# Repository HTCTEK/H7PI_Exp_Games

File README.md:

# H7PI_Exp_Games
expansion board for H7PI to use some sensors and oled

### Branch
1. master: with 1.3' oled display
2. H7PI_Exp_Games_tft: with 1.1' tft display

### Buy One
[ali taobao](https://item.taobao.com/item.htm?ft=t&id=609836748787)

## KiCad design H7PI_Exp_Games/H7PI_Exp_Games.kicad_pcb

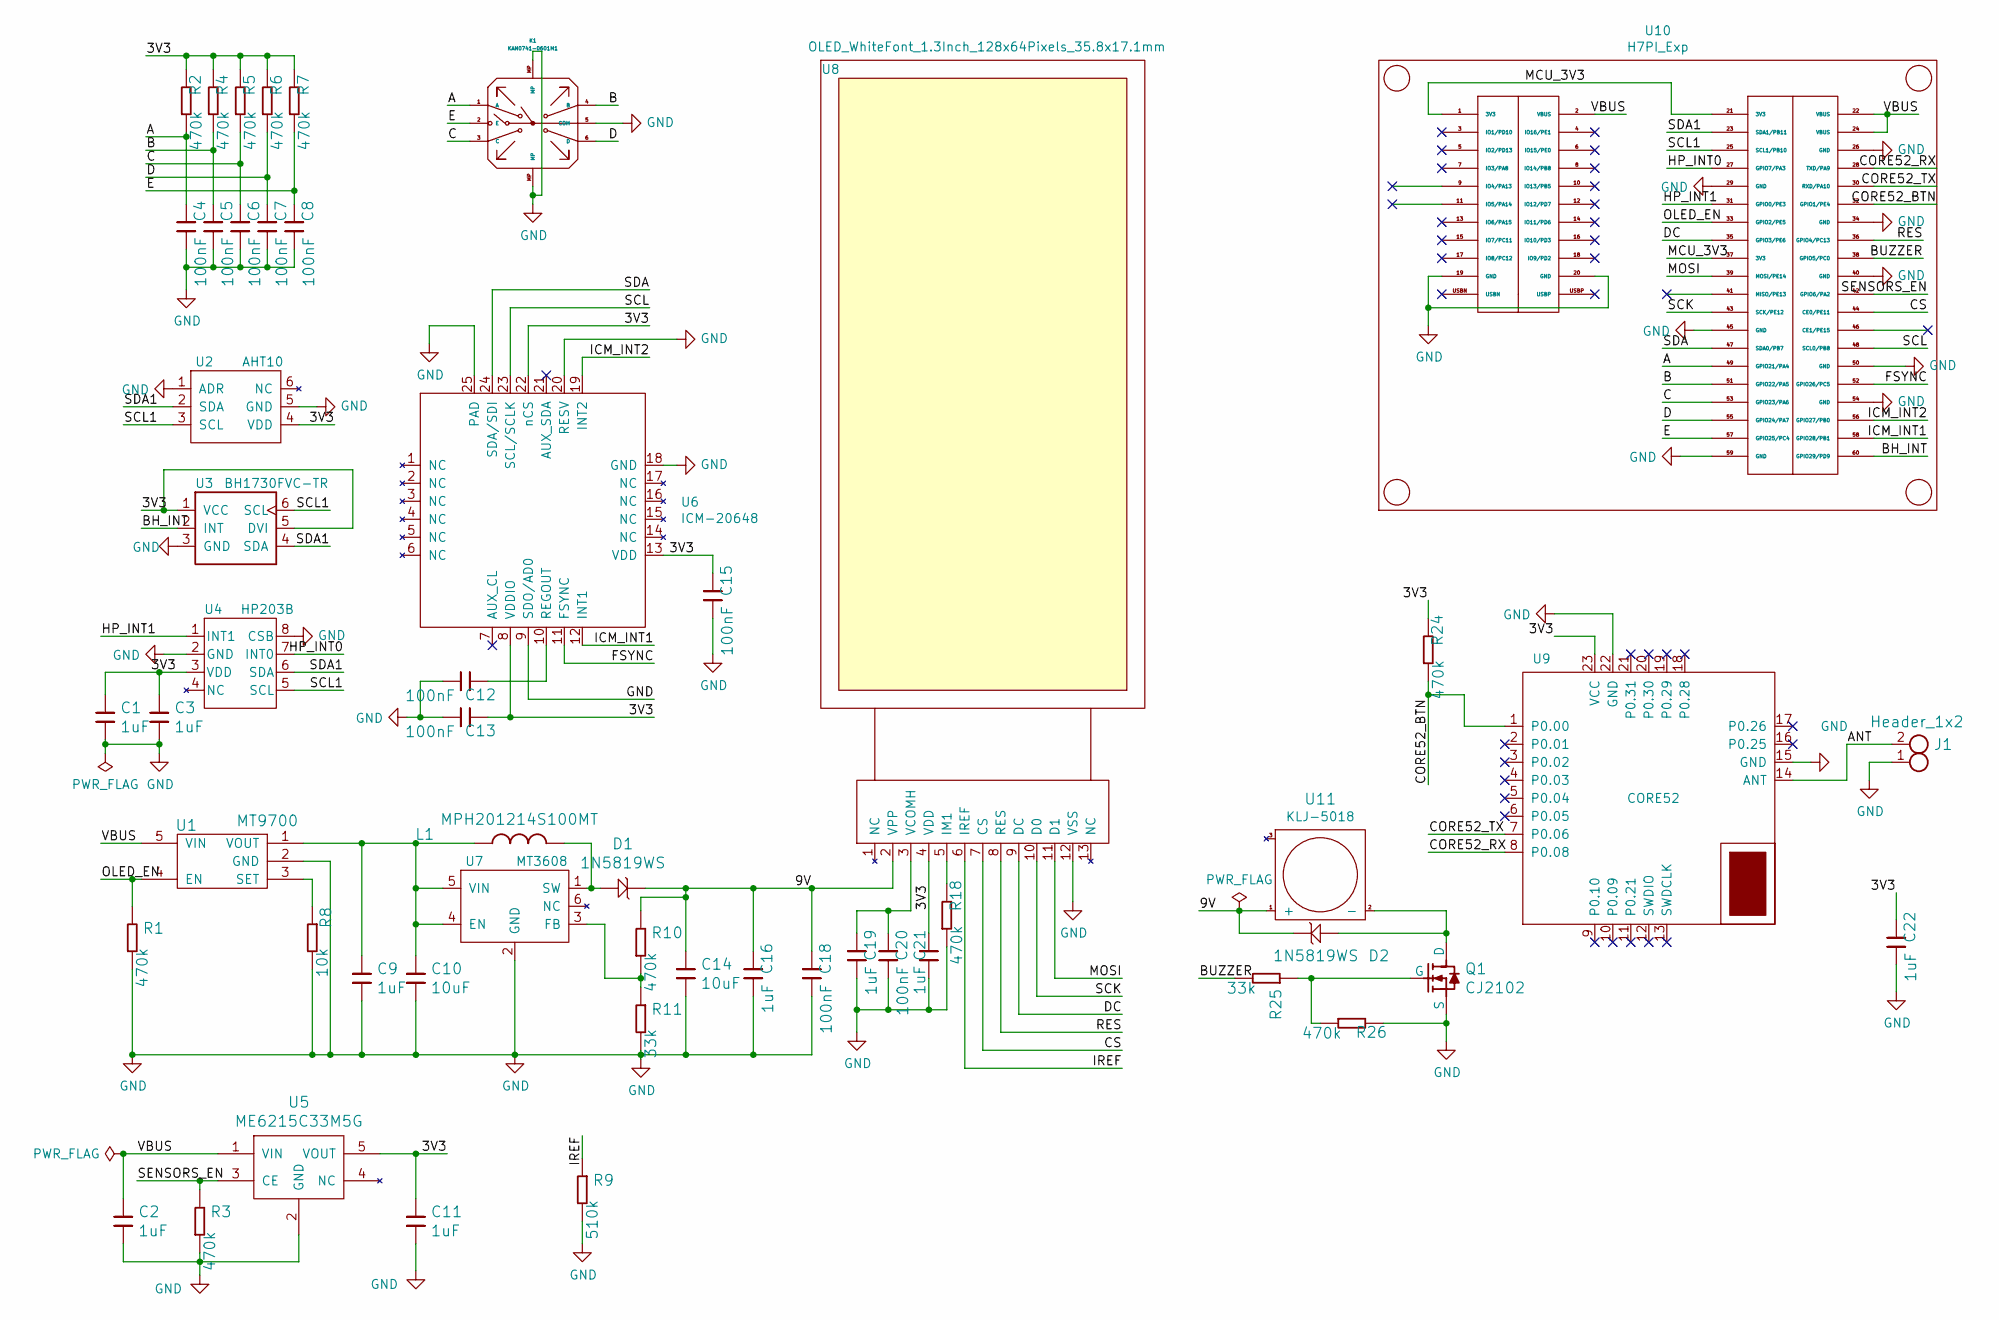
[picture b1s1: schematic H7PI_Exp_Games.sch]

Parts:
C1, C2, C3, C9, C11, C16, C19, C21, C22: 1uF; C_0603_1608Metric; PartNumber 0603B105K500NT
C4, C5, C6, C7, C8, C12, C13, C15, C18, C20: 100nF; C_0402_1005Metric; PartNumber 0402B104K500NT
C10, C14: 10uF; C_1206_3216Metric; PartNumber CL31B106KBHNNNE
D1, D2: 1N5819WS; D_SOD-323; PartNumber 1N5819WS
J1: Header_1x2; TestPoint_2Pads_Pitch2.54mm_Drill0.8mm
K1: KAN0741-0601M1; Switch_GANGYUAN_KAN0741-0601M1_TACT-SWITCH_8P_7.5x7.5x6mm; PartNumber KAN0741-0601M1
L1: MPH201214S100MT; L_0805_2012Metric; PartNumber MPH201214S100MT
Q1: CJ2102; SOT-323_SC-70; PartNumber CJ2102
R1, R2, R3, R4, R5, R6, R7, R10, R18, R24, R26: 470k; R_0402_1005Metric; PartNumber 0402WGF470KTCE
R8: 10k; R_0402_1005Metric; PartNumber 0402WGF1002TCE
R9: 510k; R_0402_1005Metric; PartNumber 0402WGF5103TCE
R11, R25: 33k; R_0402_1005Metric; PartNumber 0402WGF3302TCE
U1: MT9700; SOT-23-5; PartNumber MT9700
U2: AHT10; Temperature_Humidity_Sensor_ASAIR_AHT10_4x5x1.6mm; PartNumber AHT10
U3: BH1730FVC-TR; LightSensor_ROHM_BH1730FVC_WSOF6_2.6X1.6X0.75mm; PartNumber BH1730FVC-TR
U4: HP203B; Sensor_HP203B_HOPERF_QFN-8_3.8x3.6x1.2mm; PartNumber HP203B
U5: ME6215C33M5G; SOT-23-5; PartNumber ME6215C33M5G
U6: ICM-20648; QFN-24-1EP_3x3mm_P0.4mm_EP1.75x1.6mm; PartNumber ICM-20648
U7: MT3608; SOT-23-6; PartNumber MT3608
U8: OLED_WhiteFont_1.3Inch_128x64Pixels_35.8x17.1mm; OLED_1.3Inch_128x64Pixels_35.8x17.1x1.43mm; PartNumber GM-6428TSWOG01
U9: CORE52; Module_Bluetooth_HTCTEK_CORE52_12.5X12.5X2mm; PartNumber Core52
U10: H7PI_Exp; Module_H7PI_Exp_65x30mm; PartNumber H7PI_EXP
U11: KLJ-5018; Buzzer_KEILKING_KLJ-5018_5X5X1.8mm; PartNumber KLJ-5018

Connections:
/3V3: C1.1, C3.1, C11.1, C13.1, C15.1, C21.1, C22.1, R2.2, R4.2, R5.2, R6.2, R7.2, R24.2, U2.4 (VDD), U3.1 (VCC), U3.5 (DVI), U4.3 (VDD), U5.5 (VOUT), U6.8 (VDDIO), U6.13 (VDD), U6.22 (nCS), U8.4 (VDD), U9.23 (VCC)
/9V: C14.1, C16.1, C18.1, D1.1, D2.1, R10.2, U8.2 (VPP), U11.1 (+)
/A: C4.1, K1.1 (A), R2.1, U10.49 (GPIO21/PA4)
/ANT: J1.2, U9.14 (ANT)
/B: C5.1, K1.4 (B), R4.1, U10.51 (GPIO22/PA5)
/BH_INT: U3.2 (INT), U10.60 (GPIO29/PD9)
/BUZZER: R25.2, U10.38 (GPIO5/PC0)
/C: C6.1, K1.3 (C), R5.1, U10.53 (GPIO23/PA6)
/CORE52_BTN: R24.1, U9.1 (P0.00), U10.32 (GPIO1/PE4)
/CORE52_RX: U9.8 (P0.08), U10.28 (TXD/PA9)
/CORE52_TX: U9.7 (P0.06), U10.30 (RXD/PA10)
/CS: U8.7 (CS), U10.44 (CE0/PE11)
/D: C7.1, K1.6 (D), R6.1, U10.55 (GPIO24/PA7)
/DC: U8.9 (DC), U10.35 (GPIO3/PE6)
/E: C8.1, K1.2 (E), R7.1, U10.57 (GPIO25/PC4)
/FSYNC: U6.11 (FSYNC), U10.52 (GPIO26/PC5)
/HP_INT0: U4.7 (INT0), U10.27 (GPIO7/PA3)
/HP_INT1: U4.1 (INT1), U10.31 (GPIO0/PE3)
/ICM_INT1: U6.12 (INT1), U10.58 (GPIO28/PB1)
/ICM_INT2: U6.19 (INT2), U10.56 (GPIO27/PB0)
/IREF: R9.1, U8.6 (IREF)
/MCU_3V3: U10.1 (3V3), U10.21 (3V3), U10.37 (3V3)
/MOSI: U8.11 (D1), U10.39 (MOSI/PE14)
/OLED_EN: R1.2, U1.4 (EN), U10.33 (GPIO2/PE5)
/RES: U8.8 (RES), U10.36 (GPIO4/PC13)
/SCK: U8.10 (D0), U10.43 (SCK/PE12)
/SCL: U6.23 (SCL/SCLK), U10.48 (SCL0/PB8)
/SCL1: U2.3 (SCL), U3.6 (SCL), U4.5 (SCL), U10.25 (SCL1/PB10)
/SDA: U6.24 (SDA/SDI), U10.47 (SDA0/PB7)
/SDA1: U2.2 (SDA), U3.4 (SDA), U4.6 (SDA), U10.23 (SDA1/PB11)
/SENSORS_EN: R3.2, U5.3 (CE), U10.42 (GPIO6/PA2)
/VBUS: C2.1, U1.5 (VIN), U5.1 (VIN), U10.2 (VBUS), U10.22 (VBUS), U10.24 (VBUS)
GND: C1.2, C2.2, C3.2, C4.2, C5.2, C6.2, C7.2, C8.2, C9.2, C10.2, C11.2, C12.2, C13.2, C14.2, C15.2, C16.2, C18.2, C19.2, C20.2, C21.2, C22.2, J1.1, K1.5 (COM), K1.MP, Q1.2 (S), R1.1, R3.1, R8.2, R9.2, R11.2, R18.1, R26.2, U1.2 (GND), U2.1 (ADR), U2.5 (GND), U3.3 (GND), U4.2 (GND), U4.8 (CSB), U5.2 (GND), U6.9 (SDO/AD0), U6.18 (GND), U6.20 (RESV), U6.25 (PAD), U7.2 (GND), U8.12 (VSS), U9.15 (GND), U9.22 (GND), U10.19 (GND), U10.20 (GND), U10.26 (GND), U10.29 (GND), U10.34 (GND), U10.40 (GND), U10.45 (GND), U10.50 (GND), U10.54 (GND), U10.59 (GND)
unnamed: C9.1, C10.1, L1.1, U1.1 (VOUT), U7.4 (EN), U7.5 (VIN)
unnamed: C12.1, U6.10 (REGOUT)
unnamed: C19.1, C20.1, U8.3 (VCOMH)
unnamed: D1.2, L1.2, U7.1 (SW)
unnamed: D2.2, Q1.3 (D), U11.2 (-)
unnamed: Q1.1 (G), R25.1, R26.1
unnamed: R8.1, U1.3 (SET)
unnamed: R10.1, R11.1, U7.3 (FB)
unnamed: R18.2, U8.5 (IM1)

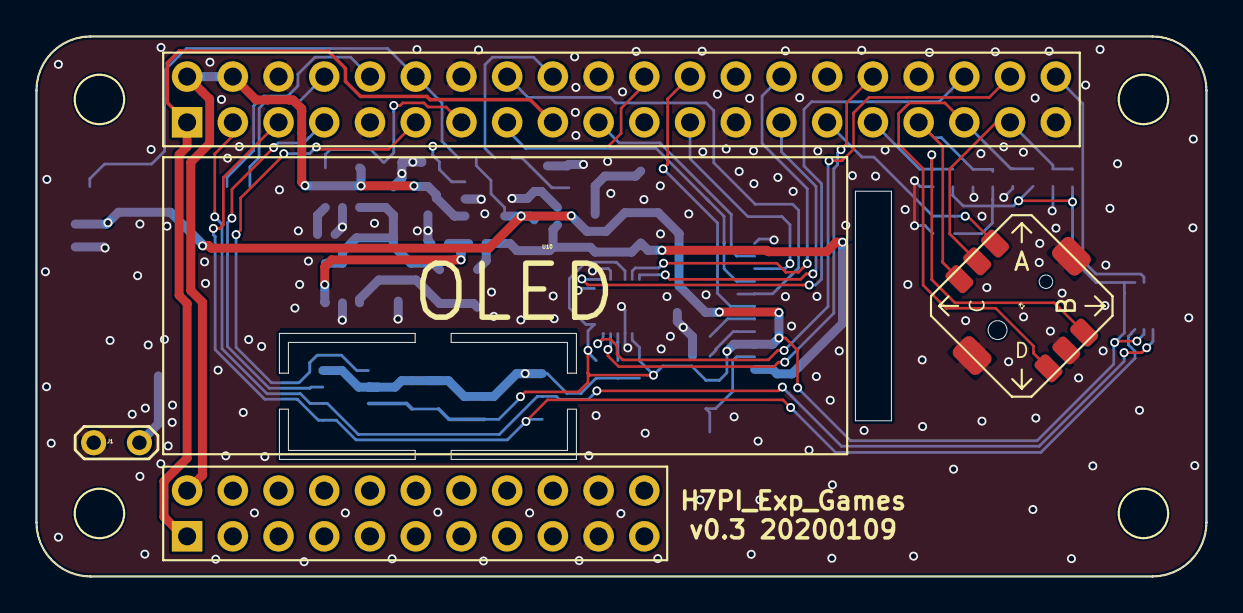
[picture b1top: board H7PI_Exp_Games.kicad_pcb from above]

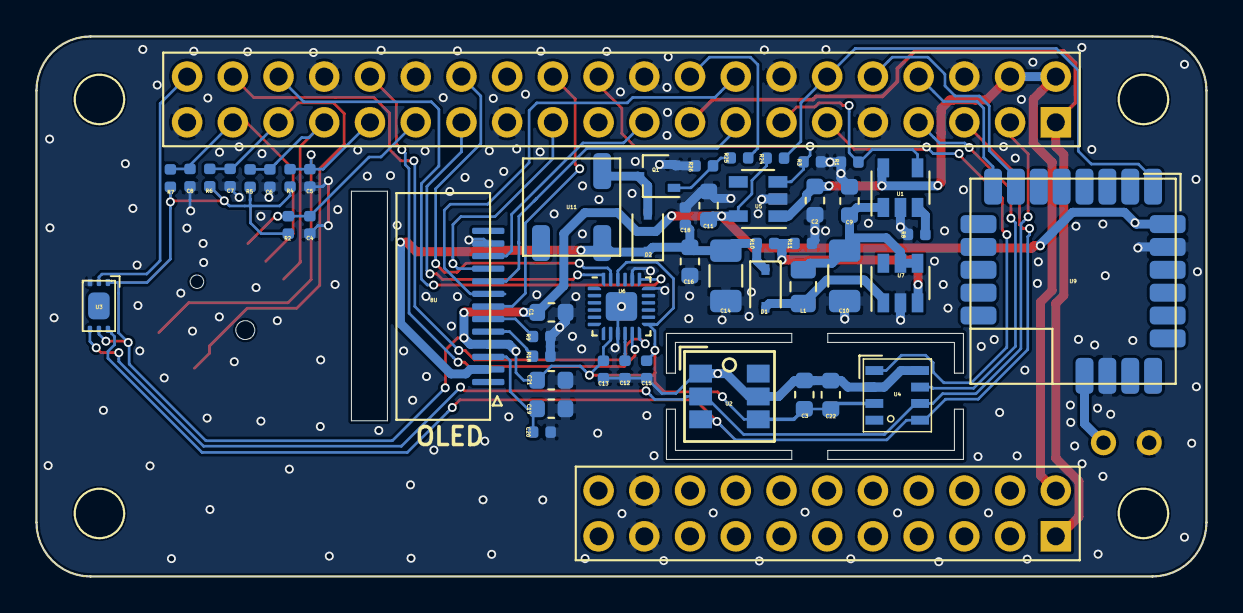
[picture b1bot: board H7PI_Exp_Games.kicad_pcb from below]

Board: 2 copper layers, 65.0 x 30.0 mm, 53 parts (49 on the bottom side), 42 nets.

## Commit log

2020-01-09 add tft branch Signed-off-by: fuhua-chen <fuhua-chen@outlook.com>
2020-01-09 v0.2 update expansion board symbol and footprint
2020-01-09 fix bug of connection of usb and copper
